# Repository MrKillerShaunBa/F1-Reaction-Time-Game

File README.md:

# F1-Reaction-Time-Game

Made this fun F1 game where we test the reaction time of the players. The LED columns light up one by one until all are on, then they turn off simultaneously. Whoever then presses their button the fastest wins!

Schematic            |  PCB         
:-------------------------:|:-------------------------:|
 |

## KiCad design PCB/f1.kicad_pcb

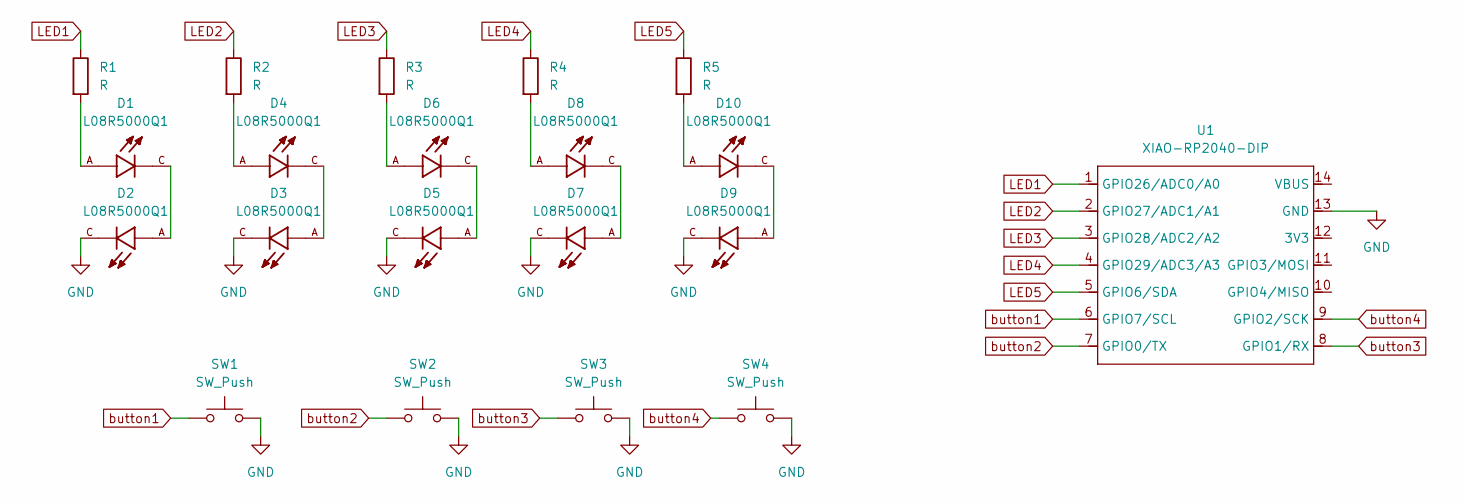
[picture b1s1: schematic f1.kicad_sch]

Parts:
D1, D2, D3, D4, D5, D6, D7, D8, D9, D10: L08R5000Q1; LEDRD254W57D500H1070; PARTREV NA
R1, R2, R3, R4, R5: R; R_Axial_DIN0204_L3.6mm_D1.6mm_P5.08mm_Horizontal
SW1, SW2, SW3, SW4: SW_Push; SW_Cherry_MX_1.00u_PCB_3D
U1: XIAO-RP2040-DIP; XIAO-RP2040-DIP_3d

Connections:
GND: D2.C, D3.C, D5.C, D7.C, D9.C, SW1.2, SW2.2, SW3.2, SW4.2, U1.13 (GND)
LED1: R1.1, U1.1 (GPIO26/ADC0/A0)
LED2: R2.1, U1.2 (GPIO27/ADC1/A1)
LED3: R3.1, U1.3 (GPIO28/ADC2/A2)
LED4: R4.1, U1.4 (GPIO29/ADC3/A3)
LED5: R5.1, U1.5 (GPIO6/SDA)
unnamed: D1.A, R1.2
unnamed: D1.C, D2.A
unnamed: D3.A, D4.C
unnamed: D4.A, R2.2
unnamed: D5.A, D6.C
unnamed: D6.A, R3.2
unnamed: D7.A, D8.C
unnamed: D8.A, R4.2
unnamed: D10.A, R5.2
unnamed: D9.A, D10.C
button1: SW1.1, U1.6 (GPIO7/SCL)
button2: SW2.1, U1.7 (GPIO0/TX)
button3: SW3.1, U1.8 (GPIO1/RX)
button4: SW4.1, U1.9 (GPIO2/SCK)

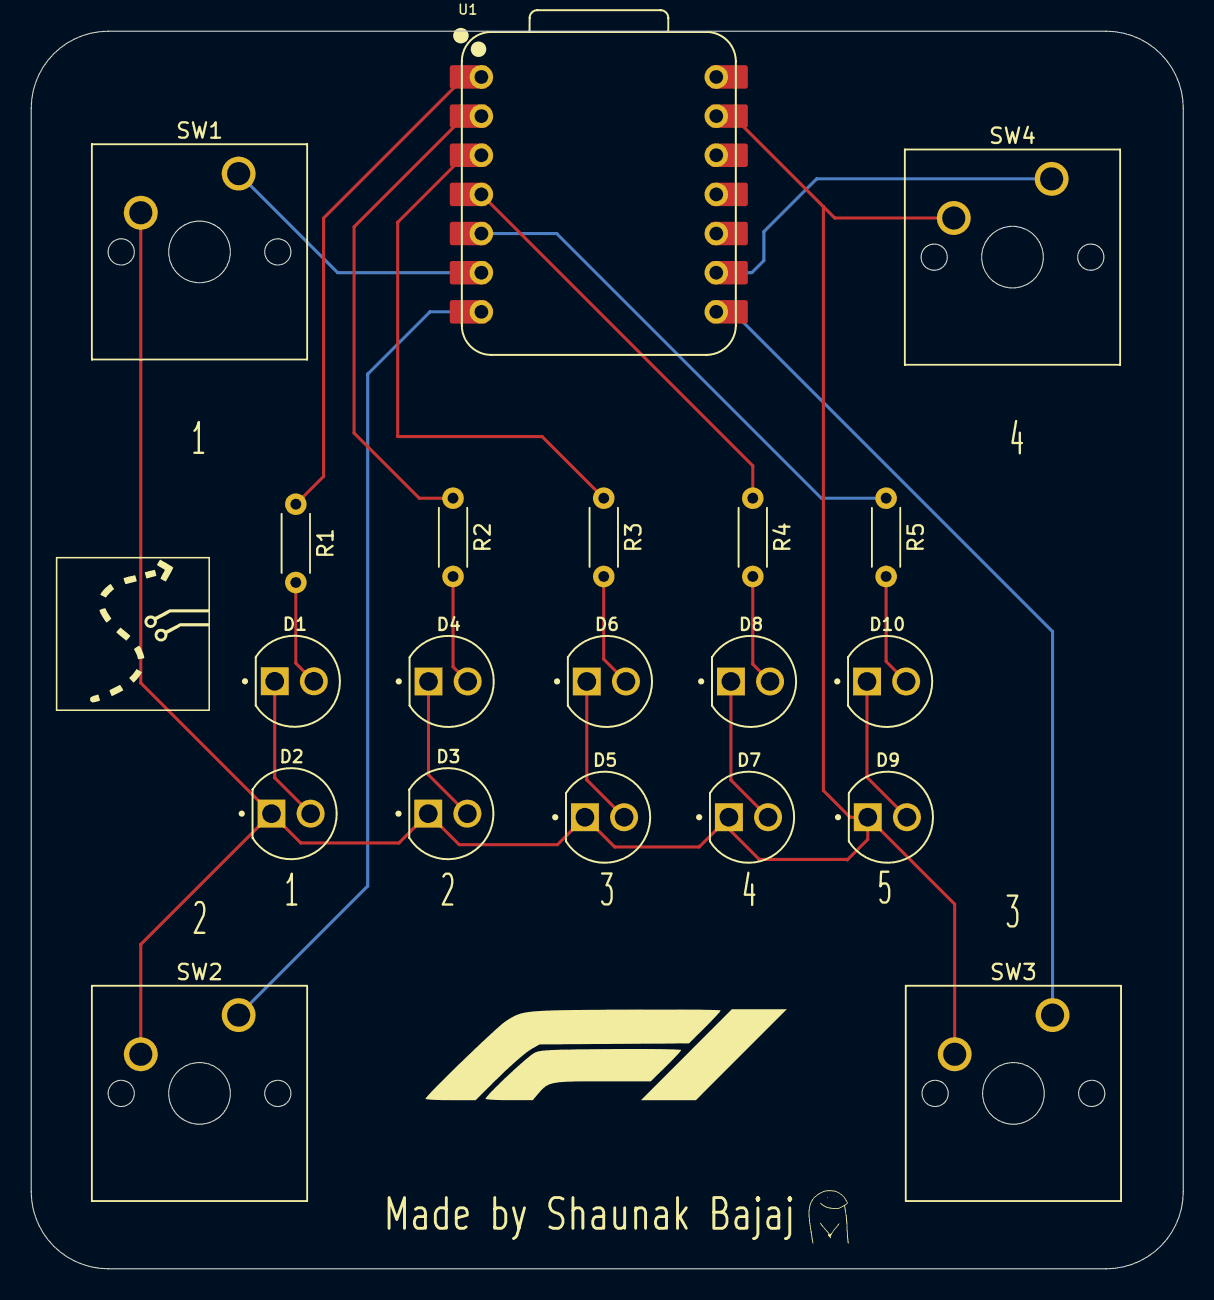
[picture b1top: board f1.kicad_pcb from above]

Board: 2 copper layers, 74.7 x 80.3 mm, 20 parts (0 on the bottom side), 20 nets.

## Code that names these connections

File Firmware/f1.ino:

int led1 = D0;
int led2 = D1;
int led3 = D2;
int led4 = D3;
int led5 = D4;

int p1 = D5;
int p2 = D6;
int p3 = D7;
int p4 = D8;

int winner = -1;
bool gameStarted = false;
bool winnerFound = false;

void setup() {
  // put your setup code here, to run once:
  pinMode(p1, INPUT_PULLUP);
  pinMode(p2, INPUT_PULLUP);
  pinMode(p3, INPUT_PULLUP);
  pinMode(p4, INPUT_PULLUP);

  pinMode(led1, OUTPUT);
  pinMode(led2, OUTPUT);
  pinMode(led3, OUTPUT);
  pinMode(led4, OUTPUT);
  pinMode(led5, OUTPUT);

  attachInterrupt(digitalPinToInterrupt(p1), p1Pressed, FALLING);
  attachInterrupt(digitalPinToInterrupt(p1), p2Pressed, FALLING);
  attachInterrupt(digitalPinToInterrupt(p3), p1Pressed, FALLING);
  attachInterrupt(digitalPinToInterrupt(p4), p2Pressed, FALLING);
}

void loop() {
  // put your main code here, to run repeatedly:
  digitalWrite(led1,LOW);
  digitalWrite(led2,LOW);
  digitalWrite(led3,LOW);
  digitalWrite(led4,LOW);
  digitalWrite(led5,LOW);

  digitalWrite(led1,HIGH);
  delay(random(200,3000));
  digitalWrite(led2,HIGH);
  delay(random(200,3000));
  digitalWrite(led3,HIGH);
  delay(random(200,3000));
  digitalWrite(led4,HIGH);
  delay(random(200,3000));
  digitalWrite(led5,HIGH);
  digitalWrite(led1,LOW);
  digitalWrite(led2,LOW);
  digitalWrite(led3,LOW);
  gameStarted = true;
  digitalWrite(led4,LOW);
  digitalWrite(led5,LOW);

   while (!winnerFound) {
    // wait
  }
  delay(1000);
  if (winner == 1){digitalWrite(led1,HIGH);}
  if (winner == 2){digitalWrite(led2,HIGH);}
  if (winner == 3){digitalWrite(led3,HIGH);}
  if (winner == 4){digitalWrite(led4,HIGH);}
  delay(3000);
  gameStarted = false;
  winnerFound = false;
  winner = -1;
}
void p1Pressed() {
  if (!gameStarted || winnerFound) return;
  winner = 1;
  winnerFound = true;
}
void p2Pressed() {
  if (!gameStarted || winnerFound) return;
  winner = 2;
  winnerFound = true;
}
void p3Pressed() {
  if (!gameStarted || winnerFound) return;
  winner = 3;
  winnerFound = true;
}
void p4Pressed() {
  if (!gameStarted || winnerFound) return;
  winner = 4;
  winnerFound = true;
}

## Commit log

2025-07-05 Rename temp.md to temp.md
